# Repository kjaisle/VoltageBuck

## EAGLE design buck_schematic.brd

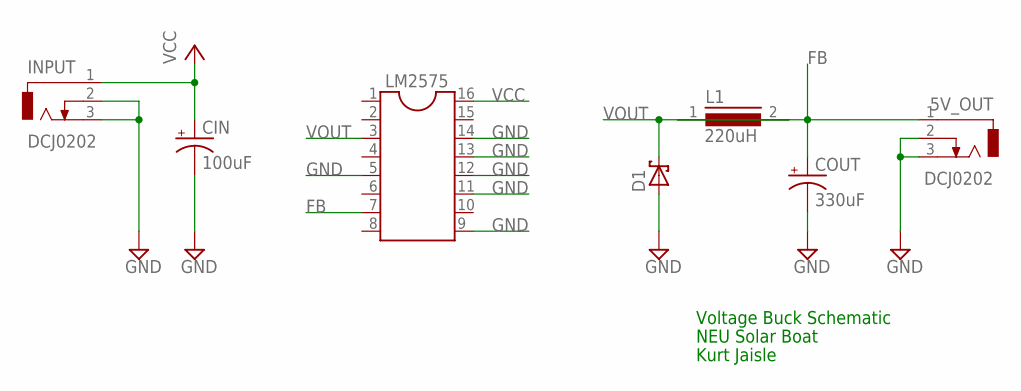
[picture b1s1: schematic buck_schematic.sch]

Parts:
5V_OUT: DCJ0202
CIN: 100uF; E5-10,5
COUT: 330uF; E5-10,5
D1: SCHOTTKY-DIODEF126Z12; F126Z12
INPUT: DCJ0202
L1: 220uH; SUKW3-27
LM2575: DIL16

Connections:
FB: 5V_OUT.1, COUT.+, L1.1, LM2575.7
GND: 5V_OUT.2, 5V_OUT.3, CIN.-, COUT.-, D1.A, INPUT.2, INPUT.3, LM2575.5, LM2575.9, LM2575.11, LM2575.12, LM2575.13, LM2575.14
VCC: CIN.+, INPUT.1, LM2575.16
VOUT: D1.C, L1.2, LM2575.3

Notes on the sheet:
Voltage Buck Schematic
Kurt Jaisle
NEU Solar Boat

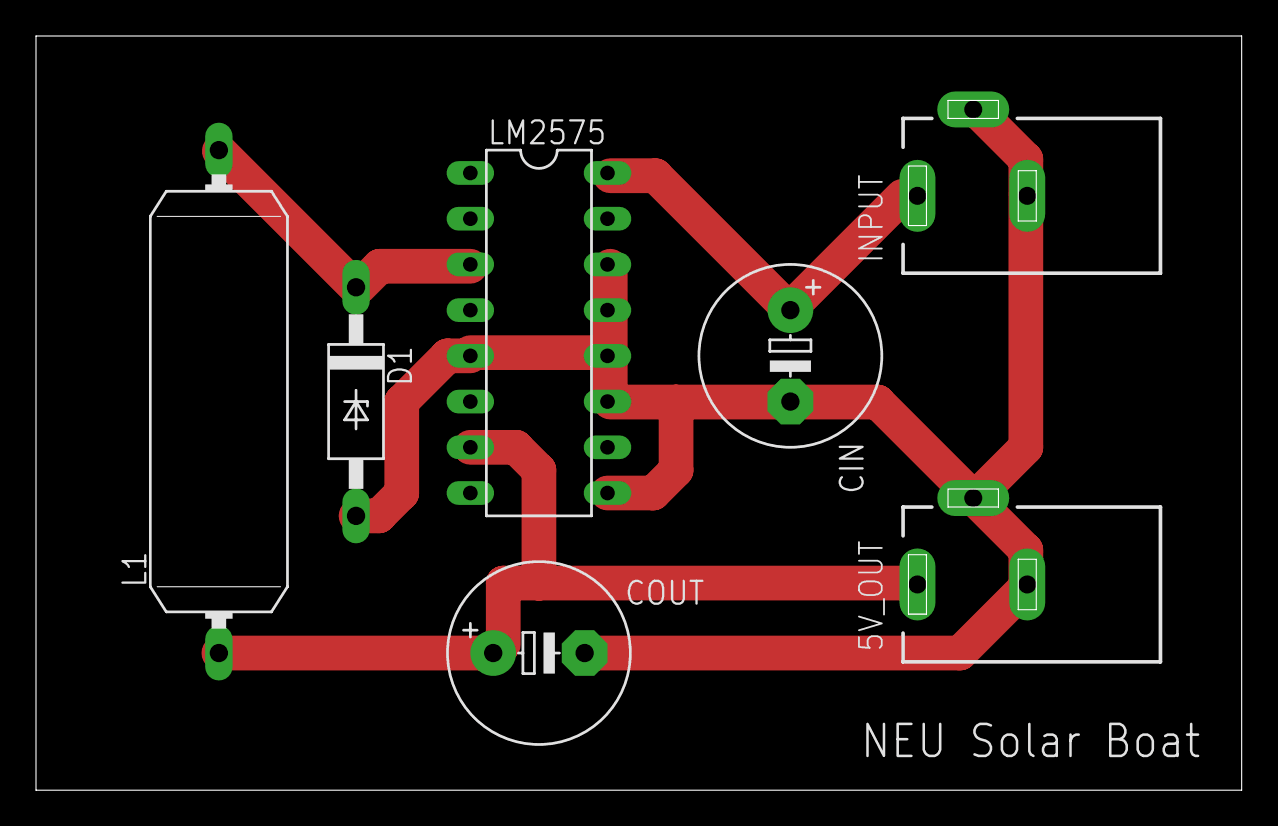
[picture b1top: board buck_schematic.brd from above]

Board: 2 copper layers, 67.0 x 41.9 mm, 7 parts (0 on the bottom side), 4 nets.

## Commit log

2015-10-24 1st version of the voltage buck schematic and layout. Ignore all the extra files in the folder, only the .brd and .sch files are important.
